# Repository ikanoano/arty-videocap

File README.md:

# arty-videocap
This is a video capture/repeater implementation on Arty-A7 the FPGA board.  
An extender board adds In/Out video ports which enables passthrough capability so that there is no delay from video source to monitor.
Captured video is sent as Motion JPEG (MJPEG) format over udp just like common cameras do.  

Right: No delay video from a game console  
Left: Video received in PC  

### RTL
hdl/MJPG_ENCODER.v and hdl/COMPONENT_ENCODER.v represent realtime MJPEG encoder.  
There is an equivalent implementation in C [here](https://github.com/ikanoano/bmp2jpeg).

### Extender board
Schematic and pcb layout are in pcb/

## How to use
### Hardware setup
1. Connect Arty, Video source, monitor and PC like below imege
2. Turn Arty and video source on
3. Once LD0, LD1 and LD2 grow, Arty starts repeating video signal to your monitor
4. Turn toggle switch SW0 on
5. Arty starts sending captured video as MJPEG stream to your PC
6. Receive MJPEG in PC using ffplay.  
`$ ffplay -f mjpeg -framerate 30 -i udp://127.0.0.1:4096`

images:[いらすとや](https://www.irasutoya.com/)

Confirmed Arty could repeat/capture 720p video sent from nintendo switch.

Your ethernet LAN hub should support jumbo frame, or jumbo frame must be disabled in RTL.  
Maybe reverting [this commit](https://github.com/ikanoano/ArtyEtherentTX/commit/a2c306d0d0775d83d8b783aa43c7d5825ad52278) works.

## How to build
### Extender board
1. Open pcb/pass_through/pass_through.pro with [kicad](http://kicad-pcb.org/)
2. Produce garbar files to order it to manufacturer. Thinner(≦0.8mm) board is better
3. Solder JP1-4, J1-2, F1-2, C1-2, C5-8, R9-18, JB1 and JC1
4. Attatch the extender board to Arty-A7 JB and JC

### RTL/Arty
1. [Install Vivado and Digilent Board Files.](https://reference.digilentinc.com/vivado/installing-vivado/start)
2. Create an RTL project. Target board should be Arty A35T
3. Import files under hdl/synth_capture/
4. [Edit destination IP address and MAC address here](https://github.com/ikanoano/ArtyEtherentTX/blob/4adc945a84c8c2099e27458f0dac0a361e1121d6/hdl/ethernet_test.vhd#L125)
5. Manually create 3 clocking modules using cloking wizard in vivado. See PASS_THROUGH.v
6. Generate bitfile
7. [Programming Arty using Quad SPI](https://reference.digilentinc.com/learn/programmable-logic/tutorials/arty-programming-guide/start?redirect=1#programming_the_arty_using_quad_spi)

## How to test MJPEG encoder RTL
Required: iverilog
1. Checkout [framehex branch at bmp2jpeg repo](https://github.com/ikanoano/bmp2jpeg/tree/output_framehex) and produce an executable
2. Convert any (small) image using 1. and you will get a simulated video signal in /tmp/frame.hex
3. Run make in hdl/
3. Run ./isim and you will get /tmp/frame.jpg, which is output from simulation. Check if it's valid

See how output jpeg will change if you reduce the value of DCT_TH_Y and DCT_TH_C in hdl/MJPG_ENCODER.v .

## License
### Except vivado-library/ and ArtyEtherentTX/
Copyright (c) 2018 ikanoano  
Released under the [MIT](https://opensource.org/licenses/mit-license.php) license

### vivado-library
Copyright (c) 2017 Digilent  
Released under the [MIT](https://opensource.org/licenses/mit-license.php) license  
See hdl/vivado-library/License.txt

## References
* [LucidScience - Build the VGA VIDEO GENERATOR](http://www.lucidscience.com/pro-vga%20video%20generator-1.aspx)
* [Xilinx - XAPP495 Implementing a TMDS Video Interface in the Spartan-6 FPGA](https://www.xilinx.com/support/documentation/application_notes/xapp495_S6TMDS_Video_Interface.pdf)
* [HDMI-NAVI.com - TMDS(Transition Minimized Differential Signaling)](http://www.hdmi-navi.com/tmds/)
* [bmp2jpeg](https://github.com/ikanoano/bmp2jpeg)

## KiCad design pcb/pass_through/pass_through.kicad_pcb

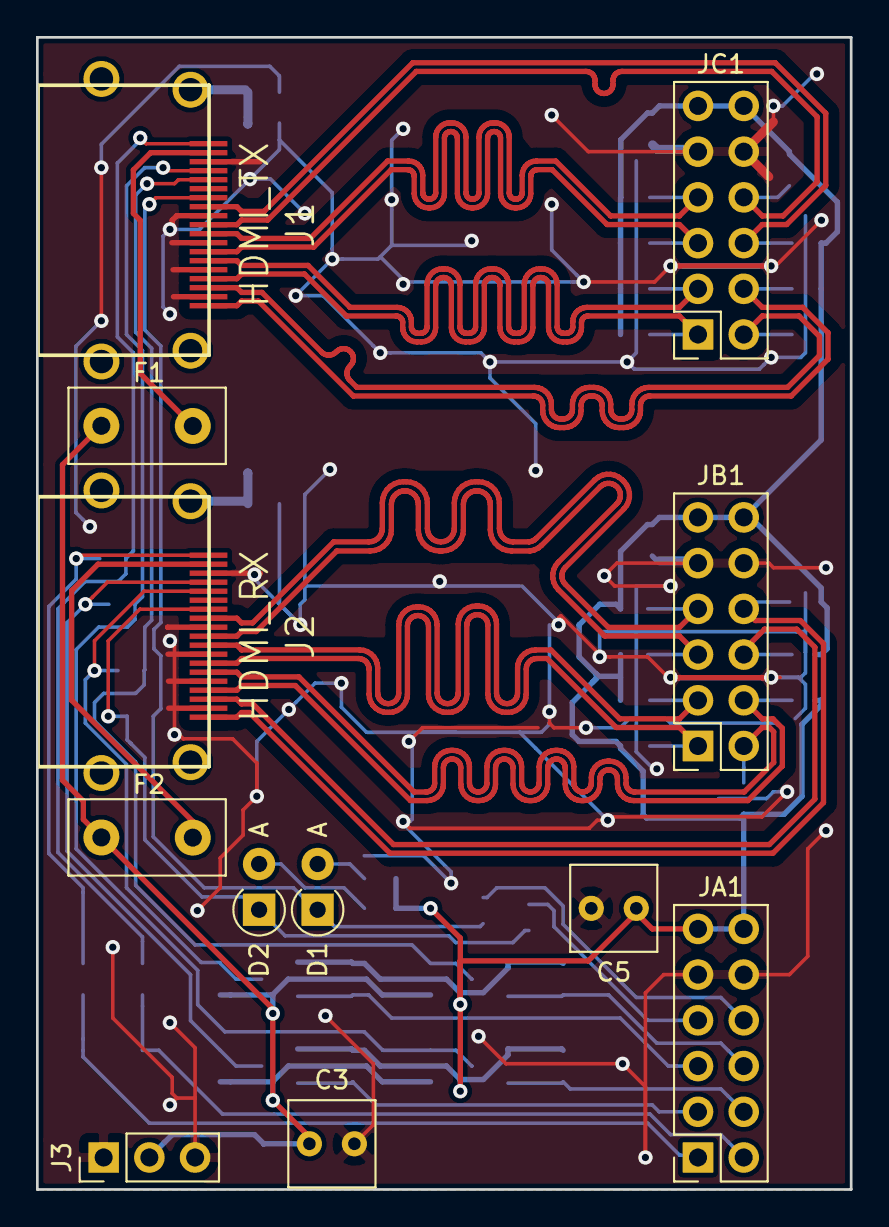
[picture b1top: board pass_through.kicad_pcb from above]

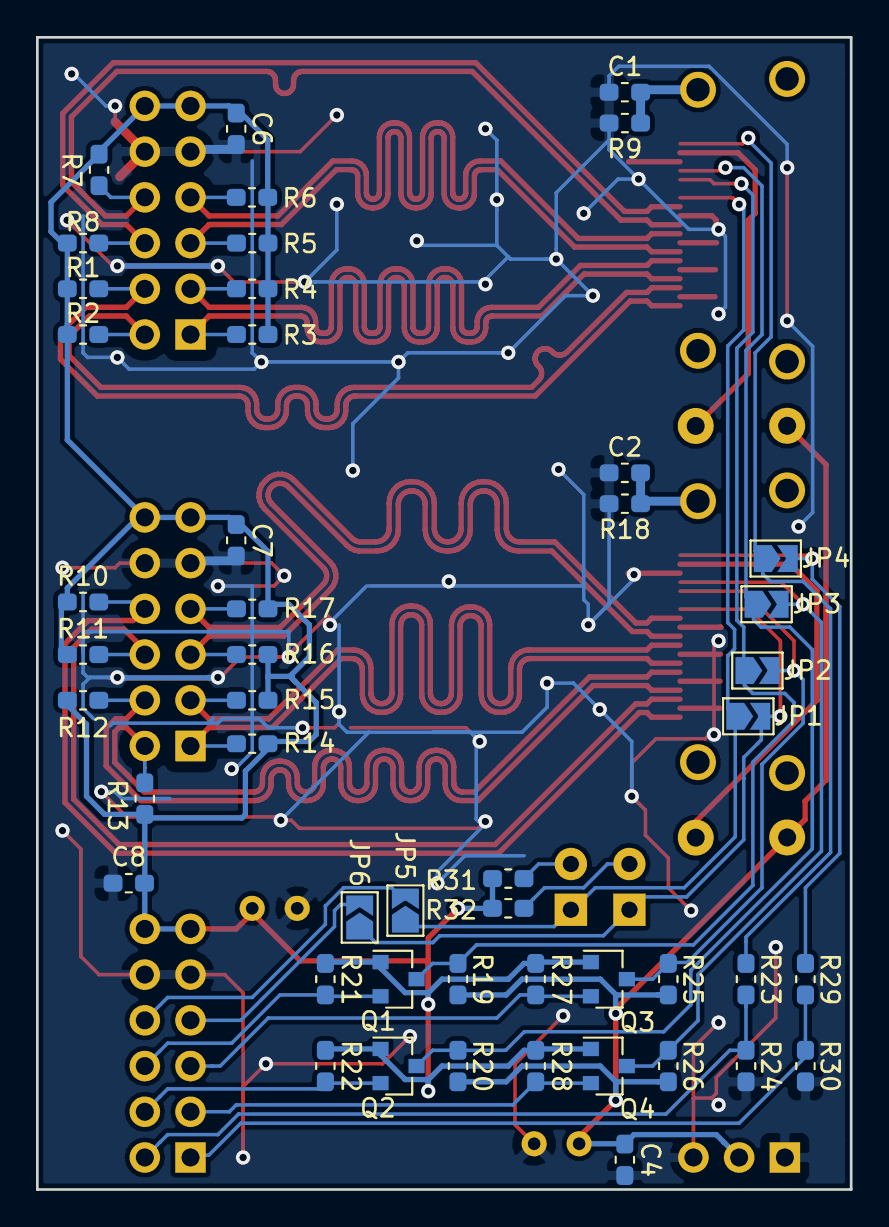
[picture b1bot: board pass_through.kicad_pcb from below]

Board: 2 copper layers, 45.2 x 64.0 mm, 60 parts (48 on the bottom side), 41 nets.

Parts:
C1, C2: 1000p; C_0603_1608Metric_Pad1.05x0.95mm_HandSolder
C3, C5: 10u; C_Rect_L4.6mm_W4.6mm_P2.50mm_MKS02_FKP02
C4, C6, C7, C8: 0.1u; C_0603_1608Metric_Pad1.05x0.95mm_HandSolder
D1, D2: D; D_A-405_P2.54mm_Vertical_AnodeUp
F1, F2: Polyfuse_Small; Fuse_Littelfuse_395Series
J1: HDMI_TX; FCI_10029449-11[13]RLF
J2: HDMI_RX; FCI_10029449-11[13]RLF
J3: Conn_01x03; PinHeader_1x03_P2.54mm_Vertical
JA1: Conn_02x06_Top_Bottom; Pmod_V
JB1: Conn_02x06_Top_Bottom; Pmod_V
JC1: Conn_02x06_Top_Bottom; Pmod_V
JP1, JP5, JP6: J_CEC; SolderJumper-2_P1.3mm_Open_TrianglePad1.0x1.5mm
JP2: J_SCL; SolderJumper-2_P1.3mm_Open_TrianglePad1.0x1.5mm
JP3: J_SDA; SolderJumper-2_P1.3mm_Open_TrianglePad1.0x1.5mm
JP4: J_HPD; SolderJumper-2_P1.3mm_Open_TrianglePad1.0x1.5mm
Q1, Q2, Q3, Q4: Q_NMOS_GSD; SOT-23
R1, R2, R3, R4, R5, R6, R7, R8, R10, R11, R12, R13, R14, R15, R16, R17: 50; R_0603_1608Metric_Pad1.05x0.95mm_HandSolder
R9, R18: 1M; R_0603_1608Metric_Pad1.05x0.95mm_HandSolder
R19, R20, R21, R22, R25, R26, R27, R28, R30: 2k; R_0603_1608Metric_Pad1.05x0.95mm_HandSolder
R23: 22k; R_0603_1608Metric_Pad1.05x0.95mm_HandSolder
R24: 33k; R_0603_1608Metric_Pad1.05x0.95mm_HandSolder
R29: 1k; R_0603_1608Metric_Pad1.05x0.95mm_HandSolder
R31, R32: 27k; R_0603_1608Metric_Pad1.05x0.95mm_HandSolder

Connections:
+5V: C3.1, C4.1, F1.1, F2.1, J3.2, R19.1, R20.1, R25.1, R26.1
/R0_N: J2.9, JB1.2, R15.2
/R0_P: J2.7, JB1.1, R14.2
/R1_N: J2.6, JB1.7, R13.2
/R1_P: J2.4, JB1.8, R12.2
/R2_N: J2.3, JB1.9, R11.2
/R2_P: J2.1, JB1.10, R10.2
/RCEC: D2.1, J2.13, JP1.2, JP6.1
/RCEC3.3: JA1.4, JP6.2
/RC_N: J2.12, JB1.4, R17.2
/RC_P: J2.10, JB1.3, R16.2
/RHPD: J2.19, JP4.2, R29.2
/RHPD3.3: JA1.1, R29.1, R30.2
/RSCL: J2.15, JP2.2, Q3.3, R25.2
/RSCL3.3: JA1.3, Q3.2, R27.2
/RSDA: J2.16, JP3.2, Q4.3, R26.2
/RSDA3.3: JA1.2, Q4.2, R28.2
/RSH: C2.2, J2.SH, R18.1
/T0_N: J1.9, JC1.4, R6.2
/T0_P: J1.7, JC1.3, R5.2
/T1_N: J1.6, JC1.2, R4.2
/T1_P: J1.4, JC1.1, R3.2
/T2_N: J1.3, JC1.7, R2.2
/T2_P: J1.1, JC1.8, R1.2
/TCEC: D1.1, J1.13, JP1.1, JP5.1
/TCEC3.3: JA1.10, JP5.2
/TC_N: J1.12, JC1.9, R8.2
/TC_P: J1.10, JC1.10, R7.2
/THPD: J1.19, JP4.1, R23.2
/THPD3.3: JA1.7, R23.1, R24.2
/TSCL: J1.15, JP2.1, Q1.3, R19.2
/TSCL3.3: JA1.9, Q1.2, R21.2
/TSDA: J1.16, JP3.1, Q2.3, R20.2
/TSDA3.3: JA1.8, Q2.2, R22.2
/TSH: C1.2, J1.SH, R9.1
GND: C1.1, C2.1, C3.2, C4.2, C5.2, C6.2, C7.2, C8.2, J1.2, J1.5, J1.8, J1.11, J1.17, J2.2, J2.5, J2.8, J2.11, J2.17, J3.1, J3.3, JA1.5, JA1.11, JB1.5, JB1.11, JC1.5, JC1.11, R9.2, R18.2, R24.1, R30.1
unnamed: D1.2, R31.2
unnamed: D2.2, R32.2
unnamed: F1.2, J1.18
unnamed: F2.2, J2.18
VCC: C5.1, C6.1, C7.1, C8.1, JA1.6, JA1.12, JB1.6, JB1.12, JC1.6, JC1.12, Q1.1, Q2.1, Q3.1, Q4.1, R1.1, R2.1, R3.1, R4.1, R5.1, R6.1, R7.1, R8.1, R10.1, R11.1, R12.1, R13.1, R14.1, R15.1, R16.1, R17.1, R21.1, R22.1, R27.1, R28.1, R31.1, R32.1

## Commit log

2018-08-17 add pcb
2018-08-17 add WIP hdl
2018-08-17 expand BITSTREAM input width
2018-08-17 add encode state machine
2018-08-18 add gitignore
2018-08-19 fix assertion
2018-08-19 fix IS_Y
2018-08-19 fix width and height detect
2018-08-19 fix u and v
2018-08-20 add signed attribute, fix eob condition
2018-08-20 fix runlen, add assertion
2018-08-20 fix ereq
2018-08-20 add stuff byte insertion
2018-08-20 add test for MJPG_ENCODER
2018-08-20 refactoring
2018-08-20 add assertion, update test
2018-08-20 add unsigned cast
2018-08-20 fix stuff byte inserter
2018-08-20 add reset value
2018-08-20 output normal format jpeg
2018-08-20 delay header and footer output to reserve space for outputting last line
2018-08-20 change DCT_TH to work correctly
2018-08-20 add makefile, update gitignore
2018-08-21 fix bsvalid, change DCT_TH_Y to be > 16
2018-08-25 add udp module
2018-08-25 remove vivado-library, update gitignore
2018-08-25 add own vivado-library
2018-08-25 add PASS_THROUGH
2018-08-26 add simple pass through
2018-08-27 stablized
2018-08-27 add filled signal, change cdc ram size
2018-08-27 add write side filled
2018-08-27 remove hsync
2018-08-28 fix clock topology
2018-08-28 avoid last line error
2018-08-28 add dbg_width
2018-08-28 change DCT_TH for ease of debugging
2018-08-28 remove redundant signed
2018-08-28 add video data output interface
2018-08-28 fix dbg_width, change initial index to output footer
2018-08-28 add modules for capture and send video
2018-08-28 fix pvalid timing
2018-08-28 add frame rate limitter, enlarge ethernet FIFO
2018-08-28 jumbo frame
2018-08-28 add color space converter
2018-08-29 add test for color space converter, fix Y
2018-08-29 fix ycbcr order
2018-08-29 invalid reg declaration, update attribute
2018-08-29 make cosine table readable for vivado
2018-08-29 tweak
2018-08-29 improve width and height detection
2018-08-29 robust hsync and vsync detection
2018-08-29 add dependency
2018-08-29 add constraints
2018-08-30 add ooc constr
2018-08-30 change input inverter
2018-08-30 add switches for ethernet enable and vsync invert
2018-08-30 add simple error reduction
2018-08-31 eye friendly brightness
2018-08-31 upgrade quality
2018-08-31 fix test
2018-08-31 fix last line output
2018-08-31 make flag not to output EOI
2018-09-04 add readme
2018-09-05 add image
2021-05-02 sanitize
